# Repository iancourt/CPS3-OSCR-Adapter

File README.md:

# CPS3 SIMM/CARTRIDGE PORT ADAPTER for OSCR

The purpose of this adapter is to provide additional methods for reading and writing CP System III cartridges and SIMM memories, utilizing the excellent open-source project [Open Source Cartridge Reader (OSCR)](https://github.com/herzmx/cartreader/).

You can enable module uncomenting **ENABLE_CPS3**, **ENABLE_FLASH8** and **ENABLE_FLASH16** in Confing.h . While the R/W implementation in OSCR is not as fast as standard flash memory programmers, it allows you to dump and flash new data without needing to desolder the flash memories from the cartridge or SIMMs.

In this version, patches have been added to change the region and CD/NOCD options, based on documented dumps from MAME.

## Compatibility

### Cartridge

You can read and write the **BIOS** from a cartridge using Fujitsu MBM29F400TC (0x0423) or MBM29F400BC (0x0422) Flash ROMs.

If you flash or write a previously dumped BIOS, as documented in the MAME [cps3.cpp](https://github.com/mamedev/mame/blob/master/src/mame/capcom/cps3.cpp), the following patches can be applied:

- Region patch
- CD/NOCD patch

**Note:** Use it at your own risk when working with live cartridges. Tested on:
 
* Red Earth **with original keys and battery**
* Street Fighter III: New Generation **with original keys and battery**
* Street Fighter III: 2nd Impact
* Street Fighter III 3rd Strike: Fight for the Futurem **with original keys and battery**
* JoJo's Venture **with original keys and battery**
* JoJo's Bizarre Adventure **with original keys and battery**
* Ultra BIOS

### SIMM's

You can read and write from 32/128Mb and 64Mb SIMMs using Fujitsu MBM29F016A (0x04AD) Flash ROMs. While CPS3 systems support multiple models of Flash ROMs, I have only tested with the Fujitsu model. Below is a list of Flash ROM models registered in the BIOS, meaning you cannot replace Flash ROMs without modifying the BIOS.

| MODEL                 | DataSheet | Physical Access |
|-----------------------|-----------|-----------------|
| MXCI MX29F016         | YES       | NO              |
| SHARP LH28F016SU      | YES       | NO              |
| INTEL 28F016SA        | YES       | NO              |
| HITACHI HN98F1600T10  | NO        | YES             |

### 32/128Mb SIMMs

The SIMM is arranged as 2x8 bits across 4 banks, with each bank handling 4MB and accessing data in 16 bits. The adapter uses an LS139 to access each bank through addresses 21 and 22.

The dump is a complete 4MB/16MB file and matches with the set of files found inside the CD-ROM. For example, SIMM 3 in *Street Fighter III 2nd Impact* corresponds to files 30+31. You can compare or write data by joining these two files.

### 64Mb SIMMs

The SIMM is arranged as 4x8 bits and accesses data in 32 bits. The adapter uses an LS245 as a bus controller to access 16 bits at a time.

The dump is a complete 8MB file and matches with the set of files from the CD-ROM. For example, SIMM 1 in *Street Fighter III 2nd Impact* corresponds to file 10, so you can write this file directly.

## Disclaimer!!!

**I am not responsible for any damage to your CPS3 cartridges or SIMMs. At this time, it remains untested in live cartridges, so use it at your own risk!**

## License
<br />This work is licensed under a <a rel="license" href="http://creativecommons.org/licenses/by-sa/4.0/">Creative Commons Attribution-ShareAlike 4.0 International License</a>. You are able to copy and redistribute the material in any medium or format, as well as remix, transform, or build upon the material for any purpose (even commercial) - but you **must** give appropriate credit, provide a link to the license, and indicate if any changes were made.

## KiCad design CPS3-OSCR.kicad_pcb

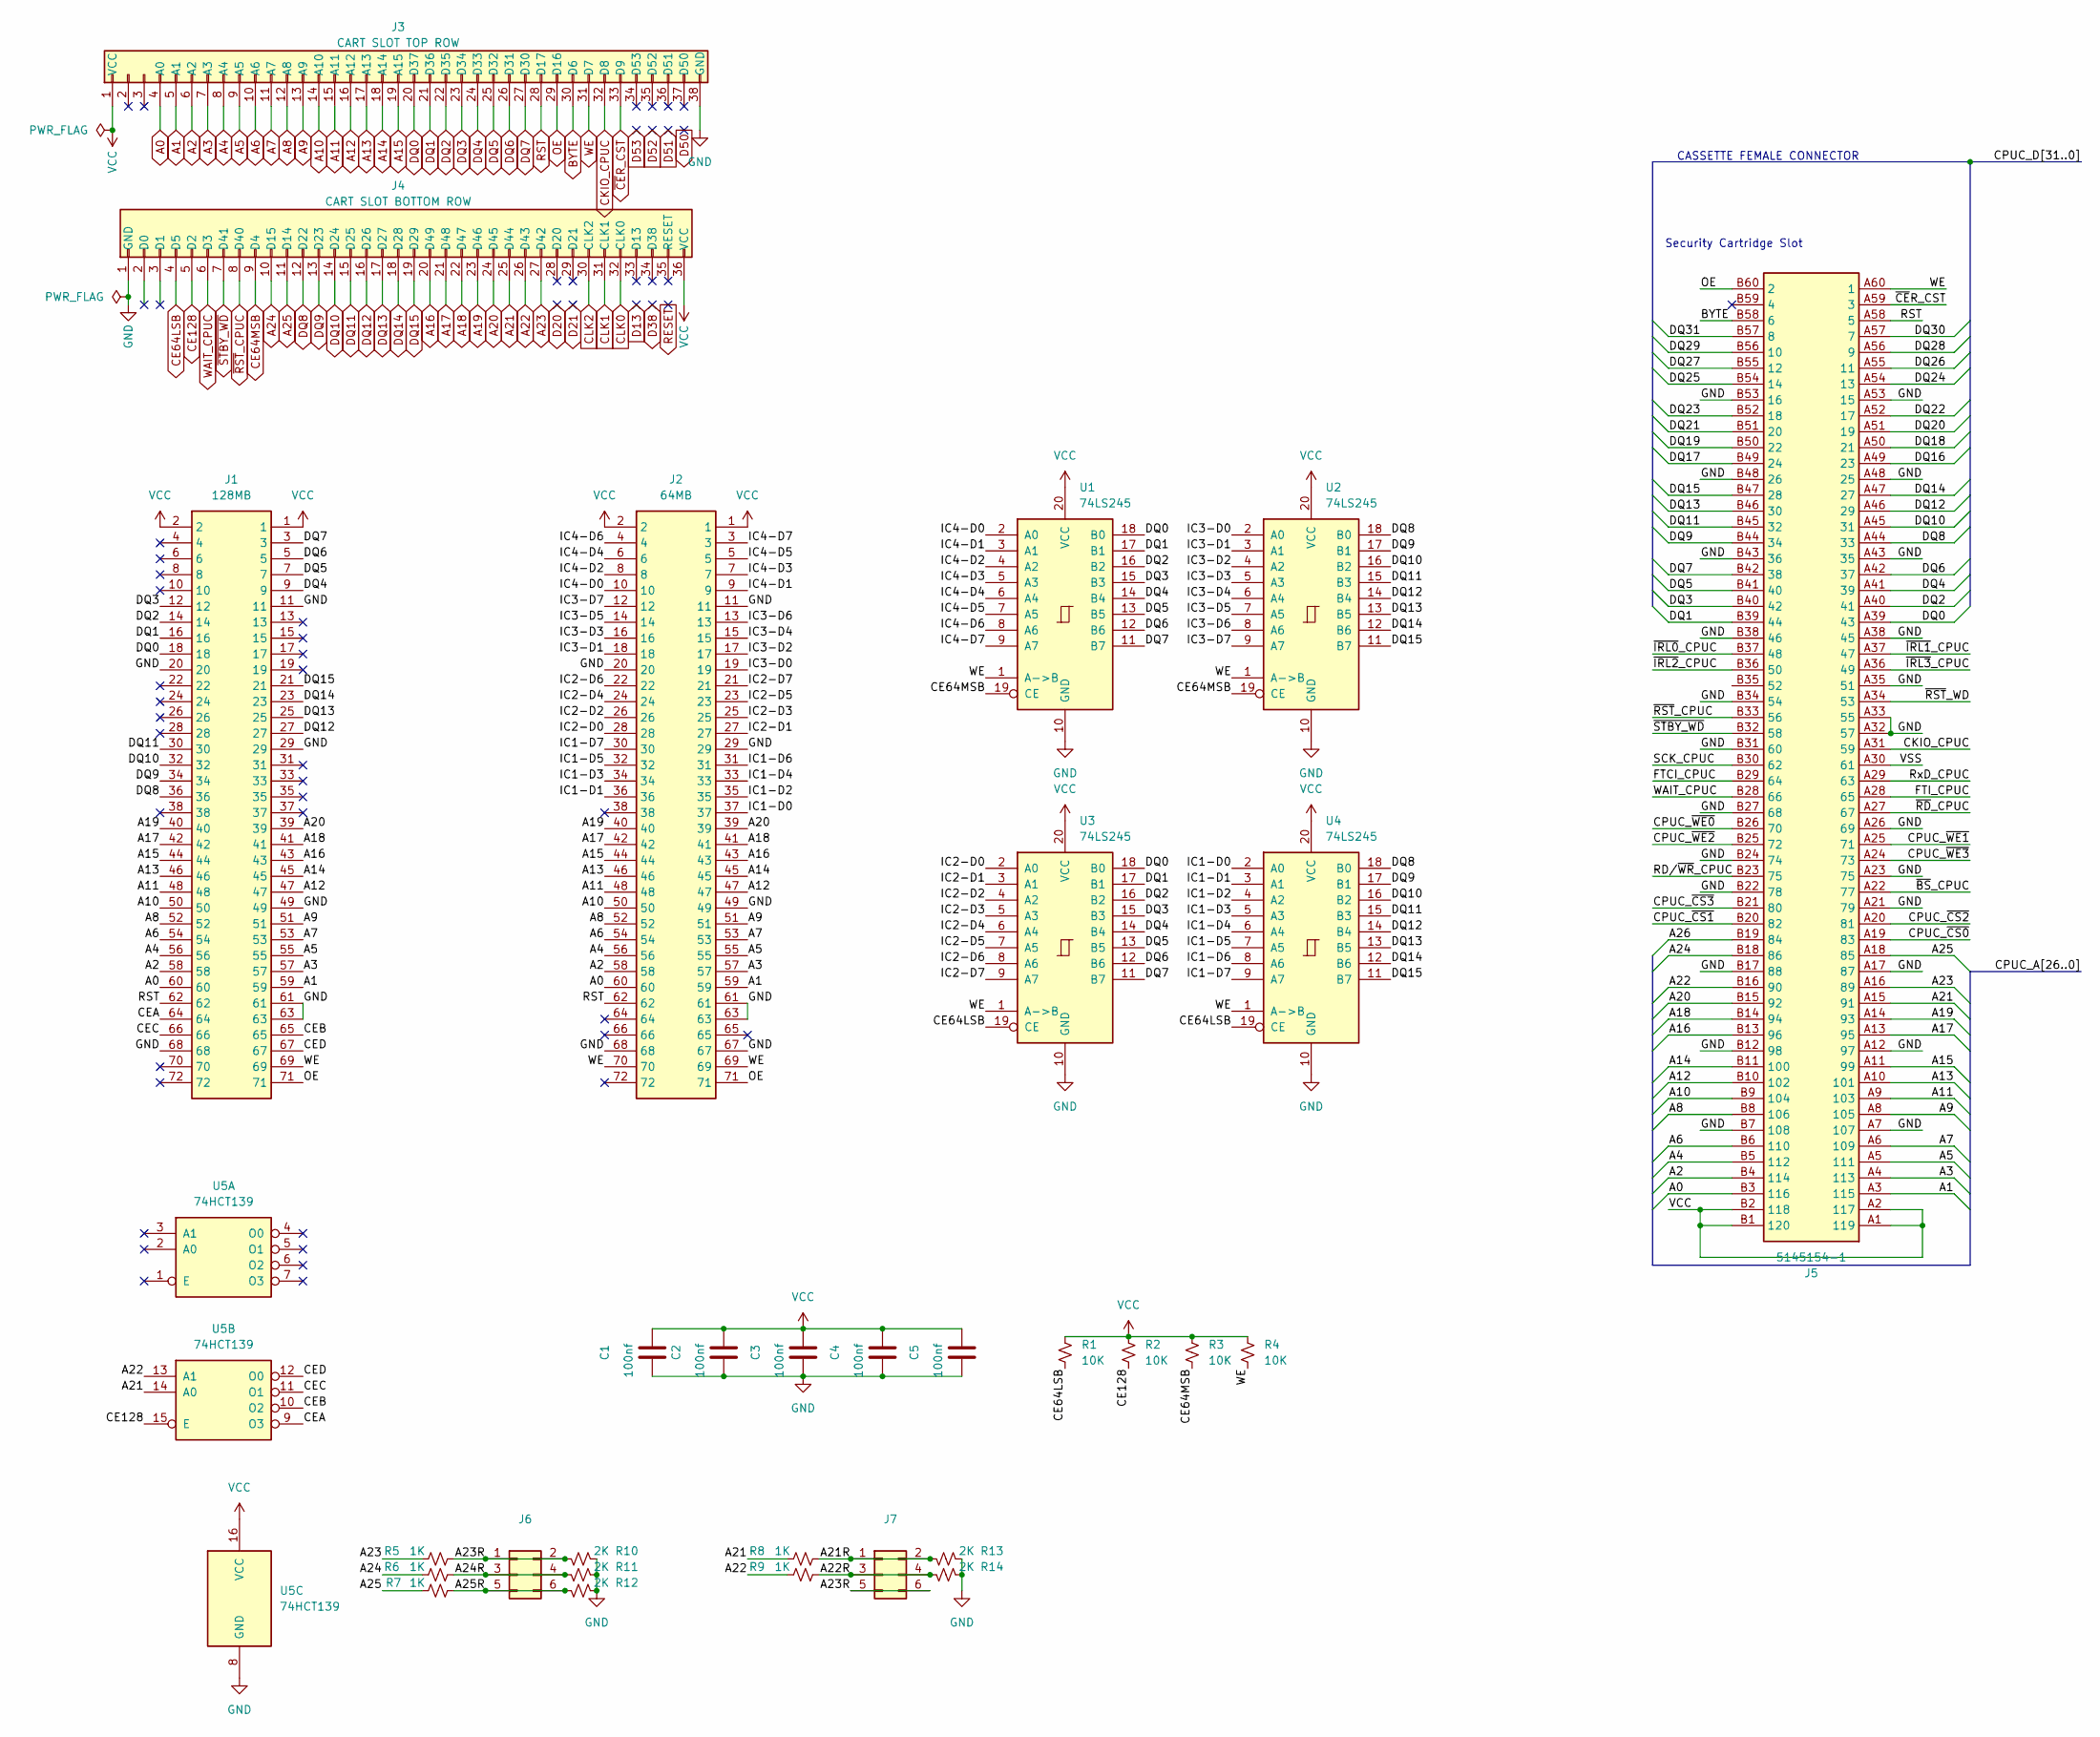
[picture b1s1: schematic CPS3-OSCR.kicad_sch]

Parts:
C1, C2, C3, C4, C5: 100nf; C_0805_2012Metric
J1: 128MB; 58220303; Manufacturer_Part_Number 5822030-3; Mouser Part Number 571-5822030-3
J2: 64MB; 58220303; Manufacturer_Part_Number 5822030-3; Mouser Part Number 571-5822030-3
J3: CART SLOT TOP ROW; PinHeader_1x38_P2.54mm_Vertical
J4: CART SLOT BOTTOM ROW; PinHeader_1x36_P2.54mm_Vertical
J5: 5145154-1; 51451541; Manufacturer_Part_Number 5145154-1; Mouser Part Number 571-5145154-1
J6, J7: Conn_02x03_Counter_Clockwise; PinHeader_2x03_P2.00mm_Vertical
R1, R2, R3, R4: 10K; R_0805_2012Metric
R5, R6, R7, R8, R9: 1K; R_0805_2012Metric
R10, R11, R12, R13, R14: 2K; R_0805_2012Metric
U1, U2, U3, U4: 74LS245; SSOP-20_5.3x7.2mm_P0.65mm_.45
U5: 74HCT139; TSSOP-16_4.4x5mm_P0.65mm

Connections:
/A21R: J7.1, J7.2, R8.2, R13.2
/A22R: J7.3, J7.4, R9.2, R14.2
/A23R: J6.1, J6.2, J7.5, J7.6, R5.2, R10.2
/A24R: J6.3, J6.4, R6.2, R11.2
/A25R: J6.5, J6.6, R7.2, R12.2
/A26: J5.B19 (84)
/CEA: J1.64, U5.9 (O3)
/CEB: J1.65, U5.10 (O2)
/CEC: J1.66, U5.11 (O1)
/CED: J1.67, U5.12 (O0)
/CPUC_~CS0: J5.A19 (83)
/CPUC_~CS1: J5.B20 (82)
/CPUC_~CS2: J5.A20 (81)
/CPUC_~CS3: J5.B21 (80)
/CPUC_~WE0: J5.B26 (70)
/CPUC_~WE1: J5.A25 (71)
/CPUC_~WE2: J5.B25 (72)
/CPUC_~WE3: J5.A24 (73)
/DQ16: J5.A49 (23)
/DQ17: J5.B49 (24)
/DQ18: J5.A50 (21)
/DQ19: J5.B50 (22)
/DQ20: J5.A51 (19)
/DQ21: J5.B51 (20)
/DQ22: J5.A52 (17)
/DQ23: J5.B52 (18)
/DQ24: J5.A54 (13)
/DQ25: J5.B54 (14)
/DQ26: J5.A55 (11)
/DQ27: J5.B55 (12)
/DQ28: J5.A56 (9)
/DQ29: J5.B56 (10)
/DQ30: J5.A57 (7)
/DQ31: J5.B57 (8)
/FTCI_CPUC: J5.B29 (64)
/FTI_CPUC: J5.A28 (65)
/IC1-D0: J2.37, U4.2 (A0)
/IC1-D1: J2.36, U4.3 (A1)
/IC1-D2: J2.35, U4.4 (A2)
/IC1-D3: J2.34, U4.5 (A3)
/IC1-D4: J2.33, U4.6 (A4)
/IC1-D5: J2.32, U4.7 (A5)
/IC1-D6: J2.31, U4.8 (A6)
/IC1-D7: J2.30, U4.9 (A7)
/IC2-D0: J2.28, U3.2 (A0)
/IC2-D1: J2.27, U3.3 (A1)
/IC2-D2: J2.26, U3.4 (A2)
/IC2-D3: J2.25, U3.5 (A3)
/IC2-D4: J2.24, U3.6 (A4)
/IC2-D5: J2.23, U3.7 (A5)
/IC2-D6: J2.22, U3.8 (A6)
/IC2-D7: J2.21, U3.9 (A7)
/IC3-D0: J2.19, U2.2 (A0)
/IC3-D1: J2.18, U2.3 (A1)
/IC3-D2: J2.17, U2.4 (A2)
/IC3-D3: J2.16, U2.5 (A3)
/IC3-D4: J2.15, U2.6 (A4)
/IC3-D5: J2.14, U2.7 (A5)
/IC3-D6: J2.13, U2.8 (A6)
/IC3-D7: J2.12, U2.9 (A7)
/IC4-D0: J2.10, U1.2 (A0)
/IC4-D1: J2.9, U1.3 (A1)
/IC4-D2: J2.8, U1.4 (A2)
/IC4-D3: J2.7, U1.5 (A3)
/IC4-D4: J2.6, U1.6 (A4)
/IC4-D5: J2.5, U1.7 (A5)
/IC4-D6: J2.4, U1.8 (A6)
/IC4-D7: J2.3, U1.9 (A7)
/RD/~WR_CPUC: J5.B23 (75)
/RxD_CPUC: J5.A29 (63)
/SCK_CPUC: J5.B30 (62)
/VSS: J5.A30 (61)
/~BS_CPUC: J5.A22 (77)
/~IRL0_CPUC: J5.B37 (48)
/~IRL1_CPUC: J5.A37 (47)
/~IRL2_CPUC: J5.B36 (50)
/~IRL3_CPUC: J5.A36 (49)
/~RD_CPUC: J5.A27 (67)
/~RST_WD: J5.A34 (53)
A0: J1.60, J2.60, J3.4 (A0), J5.B3 (116)
A1: J1.59, J2.59, J3.5 (A1), J5.A3 (115)
A2: J1.58, J2.58, J3.6 (A2), J5.B4 (114)
A3: J1.57, J2.57, J3.7 (A3), J5.A4 (113)
A4: J1.56, J2.56, J3.8 (A4), J5.B5 (112)
A5: J1.55, J2.55, J3.9 (A5), J5.A5 (111)
A6: J1.54, J2.54, J3.10 (A6), J5.B6 (110)
A7: J1.53, J2.53, J3.11 (A7), J5.A6 (109)
A8: J1.52, J2.52, J3.12 (A8), J5.B8 (106)
A9: J1.51, J2.51, J3.13 (A9), J5.A8 (105)
A10: J1.50, J2.50, J3.14 (A10), J5.B9 (104)
A11: J1.48, J2.48, J3.15 (A11), J5.A9 (103)
A12: J1.47, J2.47, J3.16 (A12), J5.B10 (102)
A13: J1.46, J2.46, J3.17 (A13), J5.A10 (101)
A14: J1.45, J2.45, J3.18 (A14), J5.B11 (100)
A15: J1.44, J2.44, J3.19 (A15), J5.A11 (99)
A16: J1.43, J2.43, J4.20 (D49), J5.B13 (96)
A17: J1.42, J2.42, J4.21 (D48), J5.A13 (95)
A18: J1.41, J2.41, J4.22 (D47), J5.B14 (94)
A19: J1.40, J2.40, J4.23 (D46), J5.A14 (93)
A20: J1.39, J2.39, J4.24 (D45), J5.B15 (92)
A21: J4.25 (D44), J5.A15 (91), R8.1, U5.14 (A0)
A22: J4.26 (D43), J5.B16 (90), R9.1, U5.13 (A1)
A23: J4.27 (D42), J5.A16 (89), R5.1
A24: J4.10 (D15), J5.B18 (86), R6.1
A25: J4.11 (D14), J5.A18 (85), R7.1
BYTE: J3.30 (D6), J5.B58 (6)
CE64LSB: J4.4 (D5), R1.2, U3.19 (CE), U4.19 (CE)
CE64MSB: J4.9 (D4), R3.2, U1.19 (CE), U2.19 (CE)
CE128: J4.5 (D2), R2.2, U5.15 (E)
CKIO_CPUC: J3.32 (D8), J5.A31 (59)
CLK0: J4.32 (CLK0)
CLK1: J4.31 (CLK1)
CLK2: J4.30 (CLK2)
DQ0: J1.18, J3.20 (D37), J5.A39 (43), U1.18 (B0), U3.18 (B0)
DQ1: J1.16, J3.21 (D36), J5.B39 (44), U1.17 (B1), U3.17 (B1)
DQ2: J1.14, J3.22 (D35), J5.A40 (41), U1.16 (B2), U3.16 (B2)
DQ3: J1.12, J3.23 (D34), J5.B40 (42), U1.15 (B3), U3.15 (B3)
DQ4: J1.9, J3.24 (D33), J5.A41 (39), U1.14 (B4), U3.14 (B4)
DQ5: J1.7, J3.25 (D32), J5.B41 (40), U1.13 (B5), U3.13 (B5)
DQ6: J1.5, J3.26 (D31), J5.A42 (37), U1.12 (B6), U3.12 (B6)
DQ7: J1.3, J3.27 (D30), J5.B42 (38), U1.11 (B7), U3.11 (B7)
DQ8: J1.36, J4.12 (D22), J5.A44 (33), U2.18 (B0), U4.18 (B0)
DQ9: J1.34, J4.13 (D23), J5.B44 (34), U2.17 (B1), U4.17 (B1)
DQ10: J1.32, J4.14 (D24), J5.A45 (31), U2.16 (B2), U4.16 (B2)
DQ11: J1.30, J4.15 (D25), J5.B45 (32), U2.15 (B3), U4.15 (B3)
DQ12: J1.27, J4.16 (D26), J5.A46 (29), U2.14 (B4), U4.14 (B4)
DQ13: J1.25, J4.17 (D27), J5.B46 (30), U2.13 (B5), U4.13 (B5)
DQ14: J1.23, J4.18 (D28), J5.A47 (27), U2.12 (B6), U4.12 (B6)
DQ15: J1.21, J4.19 (D29), J5.B47 (28), U2.11 (B7), U4.11 (B7)
GND: C1.1, C2.1, C3.1, C4.1, C5.1, J1.11, J1.20, J1.29, J1.49, J1.61, J1.63, J1.68, J2.11, J2.20, J2.29, J2.49, J2.61, J2.63, J2.67, J2.68, J3.38 (GND), J4.1 (GND), J5.A7 (107), J5.A12 (97), J5.A17 (87), J5.A21 (79), J5.A23 (75), J5.A26 (69), J5.A32 (57), J5.A33 (55), J5.A35 (51), J5.A38 (45), J5.A43 (35), J5.A48 (25), J5.A53 (15), J5.B7 (108), J5.B12 (98), J5.B17 (88), J5.B22 (78), J5.B24 (74), J5.B27 (68), J5.B31 (60), J5.B34 (54), J5.B38 (46), J5.B43 (36), J5.B48 (26), J5.B53 (16), R10.1, R11.1, R12.1, R13.1, R14.1, U1.10 (GND), U2.10 (GND), U3.10 (GND), U4.10 (GND), U5.8 (GND); also elsewhere on the board
OE: J1.71, J2.71, J3.29 (D16), J5.B60 (2)
RST: J1.62, J2.62, J3.28 (D17), J5.A58 (5)
VCC: C1.2, C2.2, C3.2, C4.2, C5.2, J1.1, J1.2, J2.1, J2.2, J3.1 (VCC), J4.36 (VCC), J5.A1 (119), J5.A2 (117), J5.B1 (120), J5.B2 (118), R1.1, R2.1, R3.1, R4.1, U1.20 (VCC), U2.20 (VCC), U3.20 (VCC), U4.20 (VCC), U5.16 (VCC)
WAIT_CPUC: J4.6 (D3), J5.B28 (66)
WE: J1.69, J2.69, J2.70, J3.31 (D7), J5.A60 (1), R4.2, U1.1 (A->B), U2.1 (A->B), U3.1 (A->B), U4.1 (A->B)
~CER_CST: J3.33 (D9), J5.A59 (3)
~RST_CPUC: J4.8 (D40), J5.B33 (56)
~STBY_WD: J4.7 (D41), J5.B32 (58)

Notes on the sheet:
Security Cartridge Slot
CASSETTE FEMALE CONNECTOR

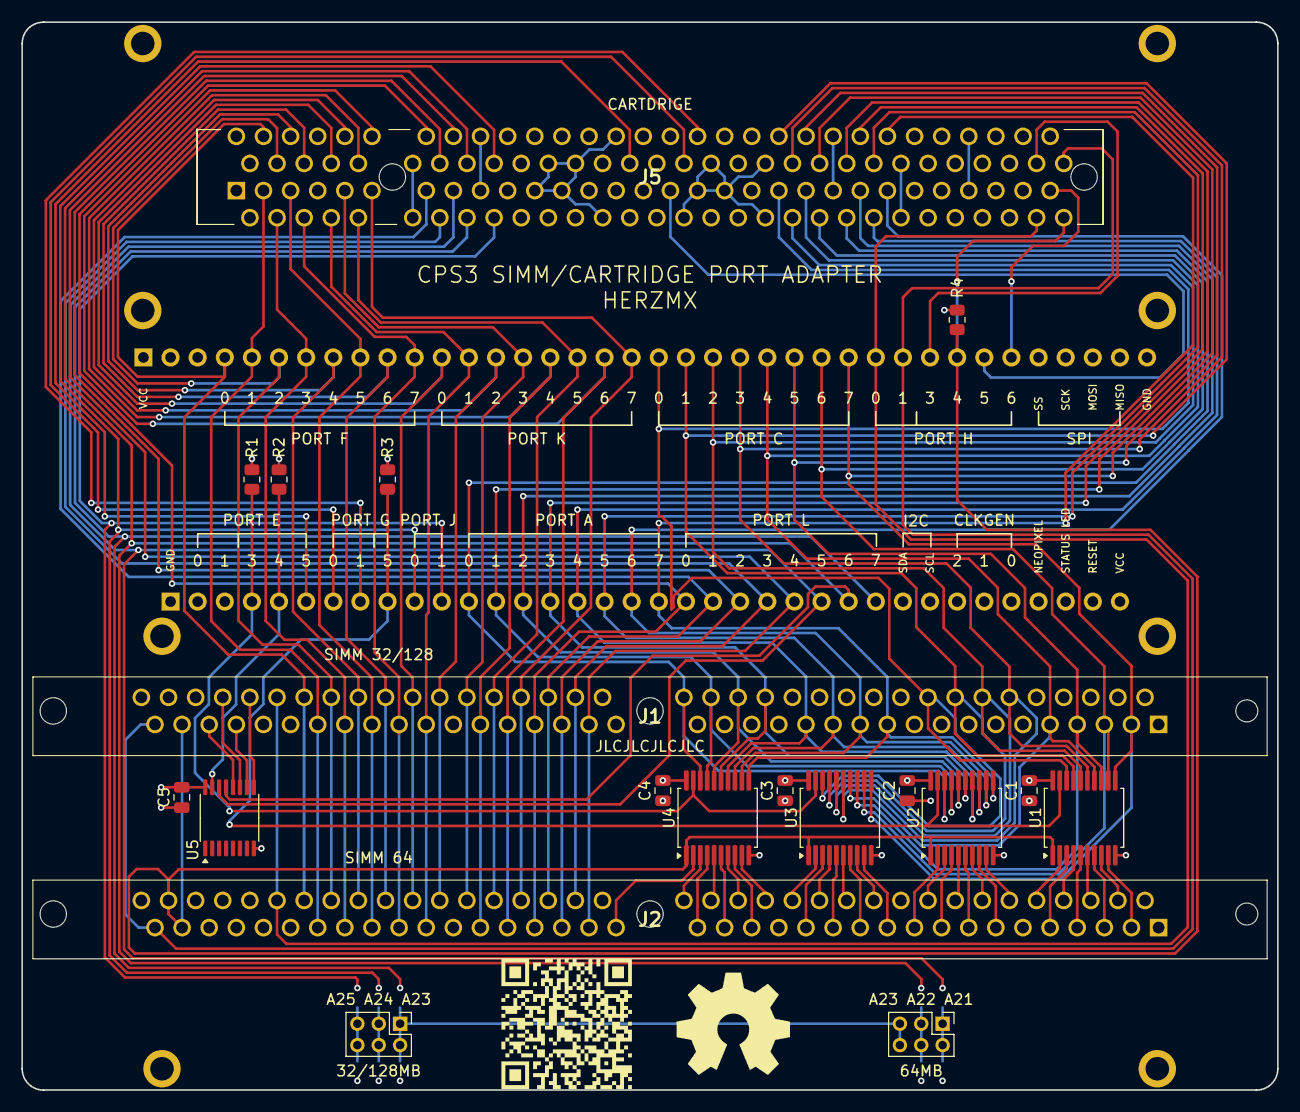
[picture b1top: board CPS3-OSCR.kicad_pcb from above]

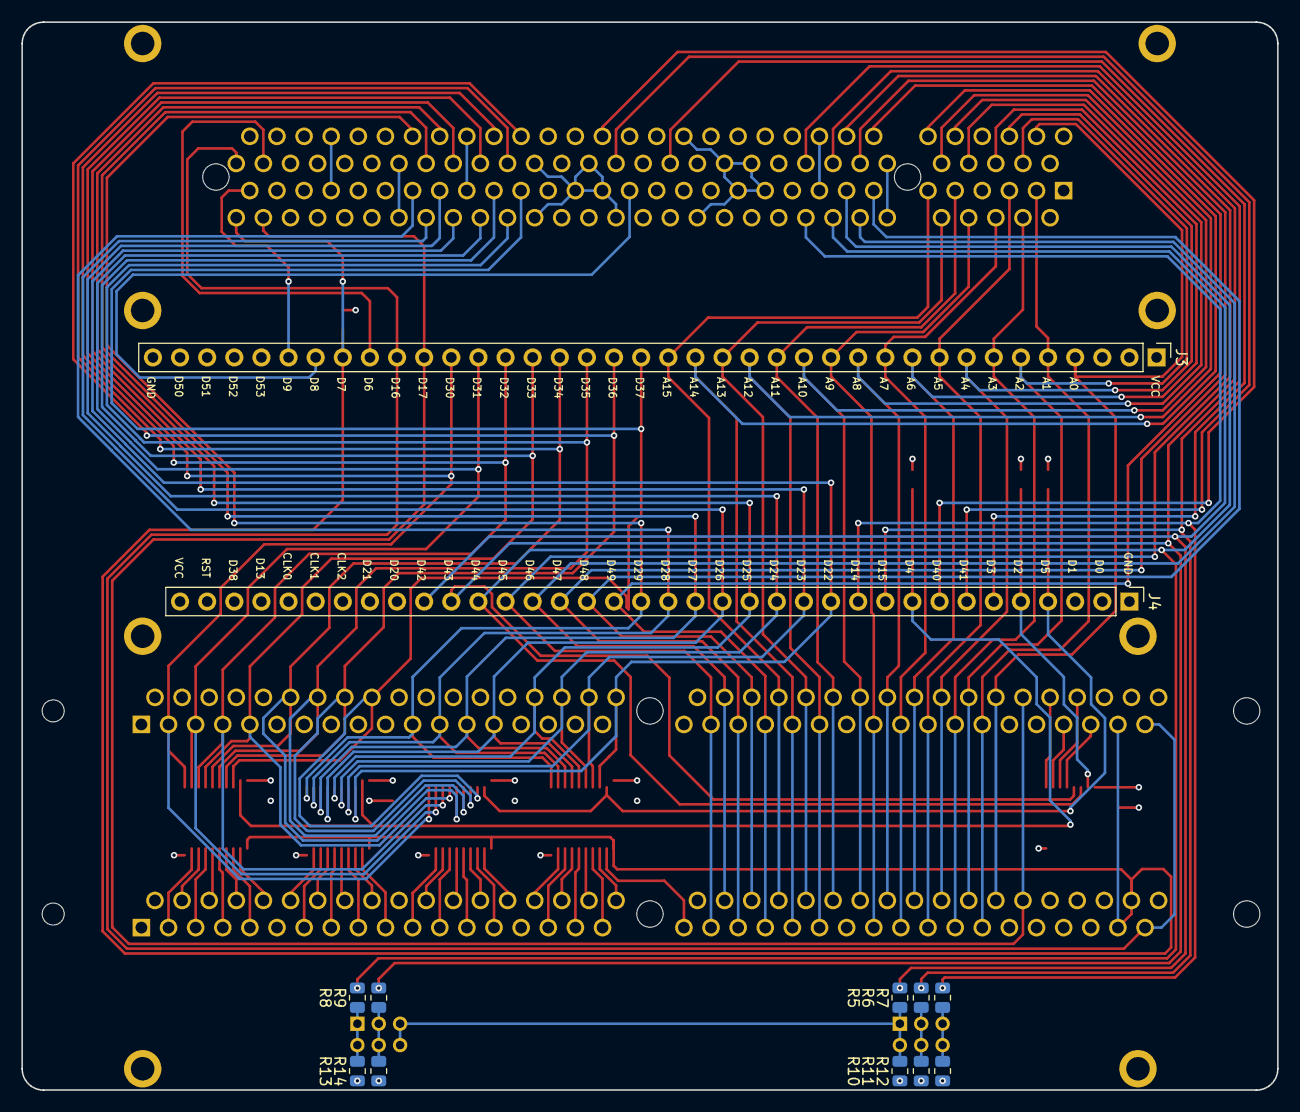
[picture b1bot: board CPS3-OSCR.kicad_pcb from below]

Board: 4 copper layers, 117.6 x 100.0 mm, 38 parts (12 on the bottom side), 97 nets.

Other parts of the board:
M2_1, M2_2, M2_3, M2_4, M2_5, M2_5#2, M2_6: Screw_Terminal_01x01; MountingHole_2.2mm_M2_ISO7380_Pad

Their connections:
GND: M2_1.1, M2_2.1, M2_5.1, M2_5#2.1, M2_6.1; also elsewhere on the board

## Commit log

2025-01-07 Add voltage divider resitor to 3.3V and pullup's disable ic's as default
2025-01-07 Update geber
2025-01-17 Update test with cartdriges with original key and battery
2025-02-14 Update BOM
2025-03-18 fix BOM
